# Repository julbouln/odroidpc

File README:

Misc files for homemade laptop based on Odroid C0 SBC (http://www.hardkernel.com/main/products/prdt_info.php?g_code=G145326484280) and various spare parts.

Audio:
- SGTL5000 sound board (https://www.pjrc.com/store/teensy3_audio.html)
- SAM2595 MIDI board (https://hackaday.io/project/6378-dream-sam2695-breakout-board)
- Stereo 3.7W Class D Audio Amplifier - MAX98306 (https://www.adafruit.com/products/987)
10)
- spare laptop Speaker (Dell Inspiron Mini 9)

Video:
- spare LP089WS1 TLA2 1024x600 LCD (Dell Inspiron Mini 9)
- HDMI to LVDS converter board (https://hackaday.io/project/13360-hdmi-to-lvds-panel-converter)

USB
- 4 port GL850G USB hub (http://asimov.n0life.org/~julbouln/electro/dotclear/index.php?post/2014/05/30/USB-Hub)
- spare laptop Keyboard (Dell Inspiron Mini 9) + homemade USB controller board
- random external mouse

Files:
- dosbox-arm: optimized dosbox (can play Warcraft 2 and Duke Nuken 3d)
- ttymidi: userspace alsa-midi board controller
- misc kernel patches

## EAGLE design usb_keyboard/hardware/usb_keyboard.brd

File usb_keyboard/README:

Dell inspiron mini 9 keyboard controller hardware + firmware using STM32F042 QFP32

TODO:
	- add Fn keys support to firmware

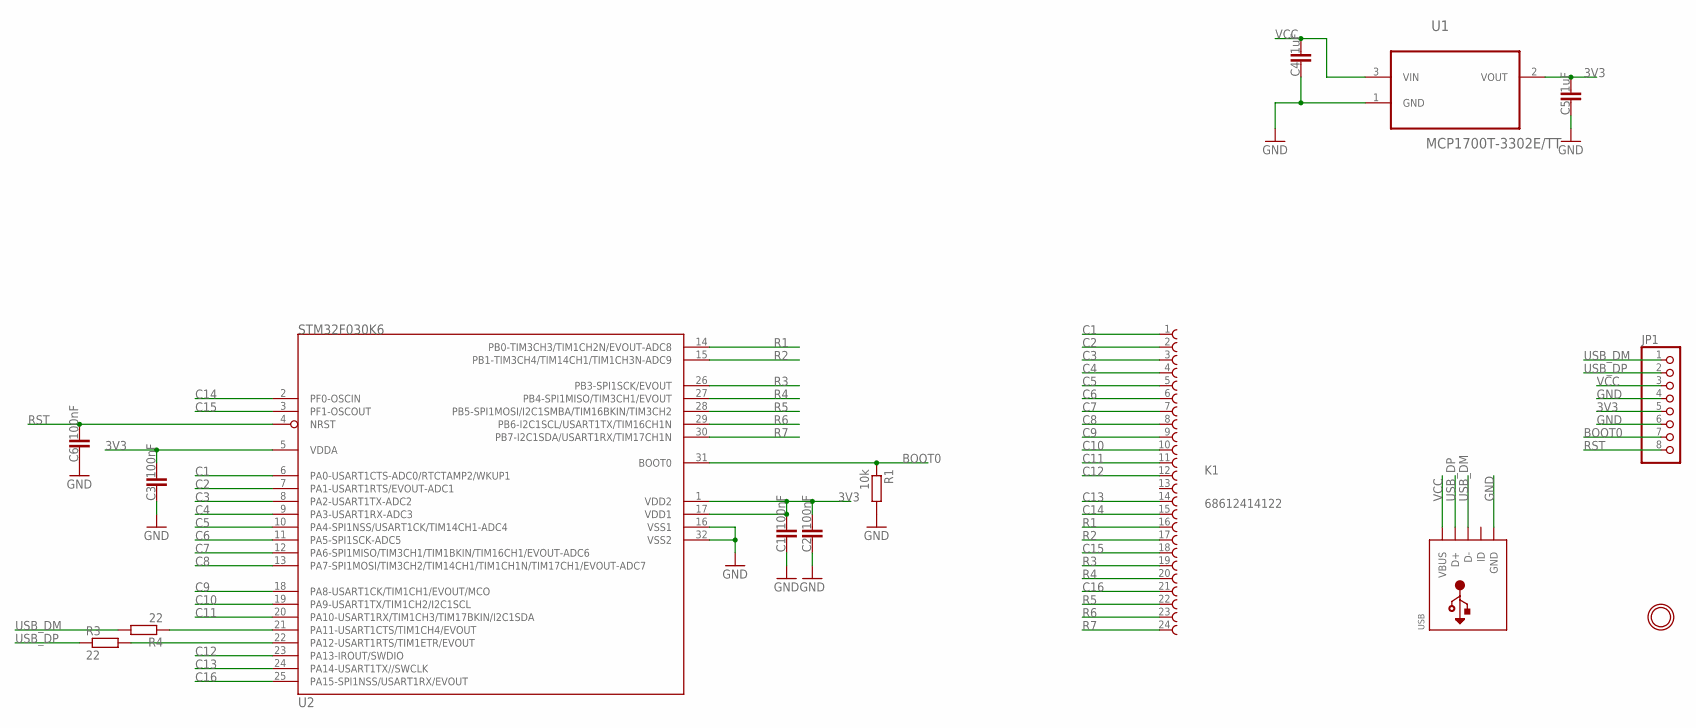
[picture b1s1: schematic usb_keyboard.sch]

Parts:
C1, C2, C3, C6: 100nF; C0603K
C4, C5: 1uF; C0603K
JP1: HEADER-1X8ROUND; 1X08_ROUND
K1: 68612414122
R1: 10k; R0603
R3, R4: 22; R0603
U1: MCP1700T-3302E/TT; SOT95P237X112-3N
U2: STM32F030K6; LQFP32
U$2: MOUNTINGHOLE2.0; MOUNTINGHOLE_2.0_PLATED
USB: USBMOLEX; USB-MINIB-THM-MOLEX

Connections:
3V3: C1.2, C2.2, C3.2, C5.2, JP1.5, U1.2 (VOUT), U2.1 (VDD2), U2.5 (VDDA), U2.17 (VDD1)
BOOT0: JP1.7, R1.1, U2.31 (BOOT0)
C1: K1.1, U2.6 (PA0-USART1CTS-ADC0/RTCTAMP2/WKUP1)
C2: K1.2, U2.7 (PA1-USART1RTS/EVOUT-ADC1)
C3: K1.3, U2.8 (PA2-USART1TX-ADC2)
C4: K1.4, U2.9 (PA3-USART1RX-ADC3)
C5: K1.5, U2.10 (PA4-SPI1NSS/USART1CK/TIM14CH1-ADC4)
C6: K1.6, U2.11 (PA5-SPI1SCK-ADC5)
C7: K1.7, U2.12 (PA6-SPI1MISO/TIM3CH1/TIM1BKIN/TIM16CH1/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)
C8: K1.8, U2.13 (PA7-SPI1MOSI/TIM3CH2/TIM14CH1/TIM1CH1N/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)
C9: K1.9, U2.18 (PA8-USART1CK/TIM1CH1/EVOUT/MCO)
C10: K1.10, U2.19 (PA9-USART1TX/TIM1CH2/I2C1SCL)
C11: K1.11, U2.20 (PA10-USART1RX/TIM1CH3/TIM17BKIN/I2C1SDA)
C12: K1.12, U2.23 (PA13-IROUT/SWDIO)
C13: K1.14, U2.24 (PA14-USART1TX//SWCLK)
C14: K1.15, U2.2 (PF0-OSCIN)
C15: K1.18, U2.3 (PF1-OSCOUT)
C16: K1.21, U2.25 (PA15-SPI1NSS/USART1RX/EVOUT)
GND: C1.1, C2.1, C3.1, C4.1, C5.1, C6.1, JP1.4, JP1.6, R1.2, U1.1 (GND), U2.16 (VSS1), U2.32 (VSS2), USB.GND
unnamed: R4.1, U2.21 (PA11-USART1CTS/TIM1CH4/EVOUT)
unnamed: R3.2, U2.22 (PA12-USART1RTS/TIM1ETR/EVOUT)
R1: K1.16, U2.14 (PB0-TIM3CH3/TIM1CH2N/EVOUT-ADC8)
R2: K1.17, U2.15 (PB1-TIM3CH4/TIM14CH1/TIM1CH3N-ADC9)
R3: K1.19, U2.26 (PB3-SPI1SCK/EVOUT)
R4: K1.20, U2.27 (PB4-SPI1MISO/TIM3CH1/EVOUT)
R5: K1.22, U2.28 (PB5-SPI1MOSI/I2C1SMBA/TIM16BKIN/TIM3CH2)
R6: K1.23, U2.29 (PB6-I2C1SCL/USART1TX/TIM16CH1N)
R7: K1.24, U2.30 (PB7-I2C1SDA/USART1RX/TIM17CH1N)
RST: C6.2, JP1.8, U2.4 (NRST)
USB_DM: JP1.1, R4.2, USB.D-
USB_DP: JP1.2, R3.1, USB.D+
VCC: C4.2, JP1.3, U1.3 (VIN), USB.VBUS

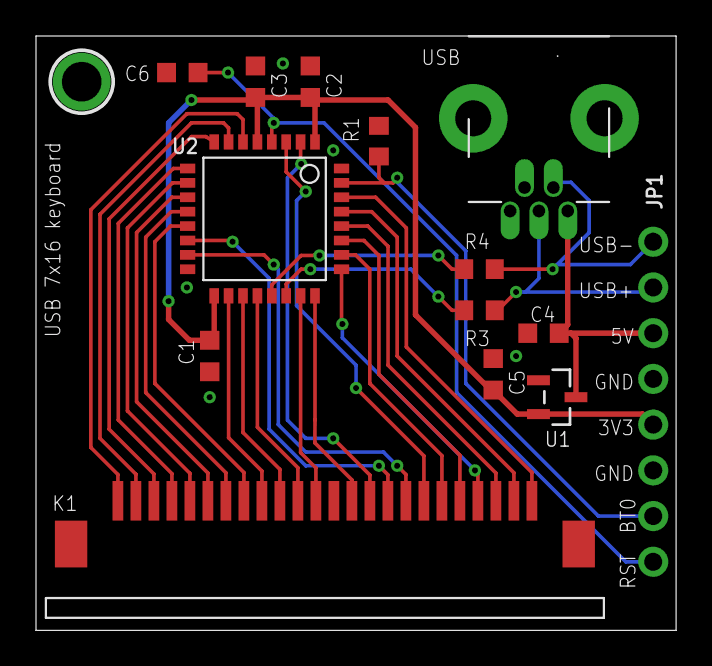
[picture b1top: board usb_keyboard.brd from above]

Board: 2 copper layers, 35.6 x 33.0 mm, 15 parts (0 on the bottom side), 32 nets.

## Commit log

2017-01-07 experimental full interrupt kbd matrix
2017-01-24 fix int

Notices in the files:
parts and their libraries:
FPC_Connectors_Flat_Flexible_Cable_rev15: Copyright: Würth Elektronik
microbuilder: This work is placed in the public domain, and may be freely used for commercial and non-commercial work with the following conditions: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
